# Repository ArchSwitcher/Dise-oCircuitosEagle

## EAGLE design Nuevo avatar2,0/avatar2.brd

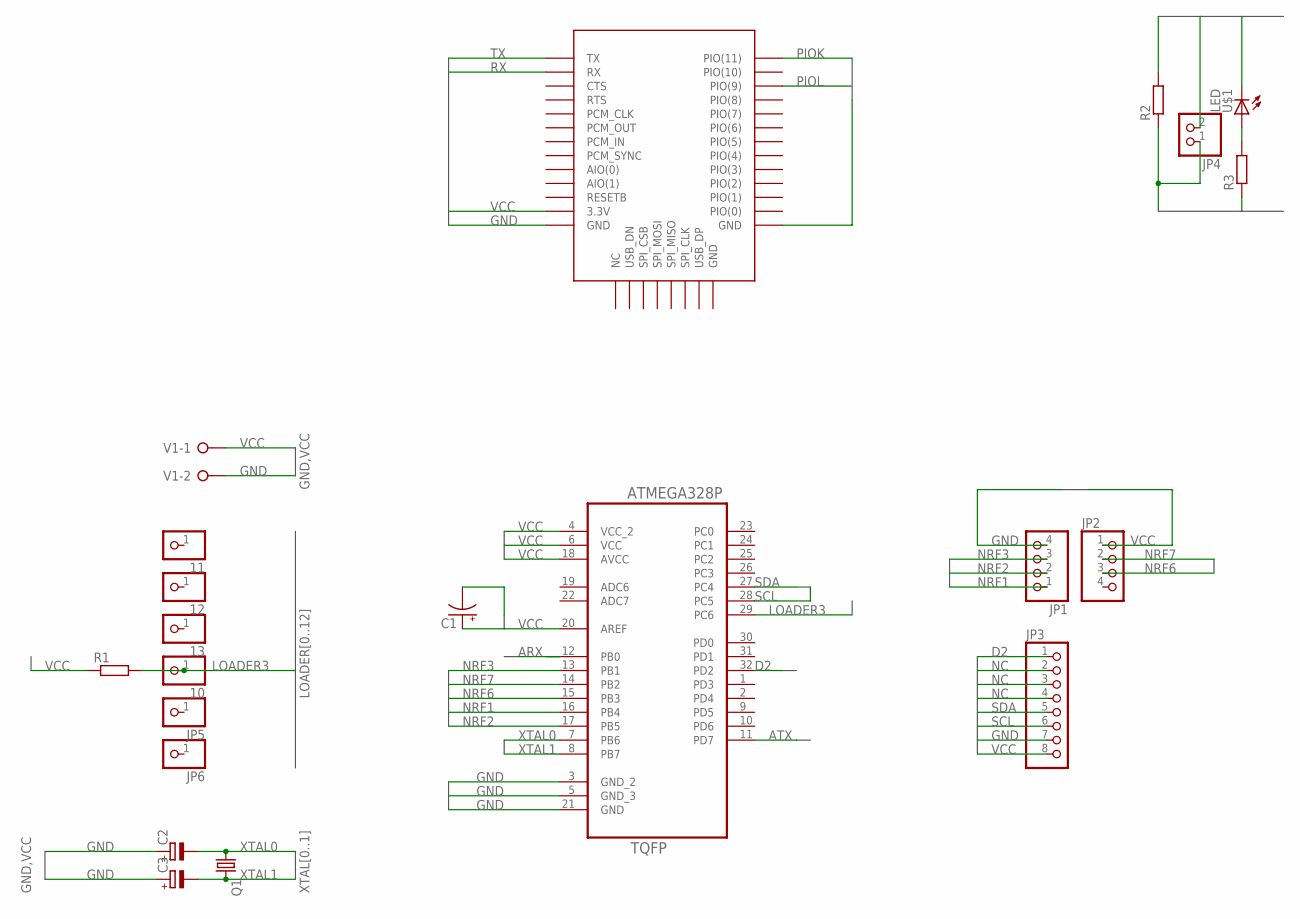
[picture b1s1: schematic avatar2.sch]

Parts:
10, 11, 12, 13: PINHD-1X1; 1X01
C1: CPOL-USTT5D7; TT5D7
C2, C3: CPOL-EUE1.8-4; E1,8-4
IC1: BC04_BLUETOOTH; BC04
JP1, JP2: PINHD-1X4; 1X04
JP3: PINHD-1X8; 1X08
JP4: PINHD-1X2; 1X02
JP5, JP6: PINHD-1X1; 1X01
Q1: CRYSTALHC49U-V; HC49U-V
R1, R2, R3: R0207/10; 0207/10
U1: ATMEGA328P-AU; QFP80P900X900X120-32N
U$1: LED; HLMP-1790
V1: W237-02P; W237-132

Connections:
ARX: U1.12 (PB0)
ATX: U1.11 (PD7)
D2: JP3.1, U1.32 (PD2)
GND: C1.-, C2.+, C3.+, IC1.P$13 (GND), IC1.P$22 (GND), JP1.4, JP3.7, R2.2, U1.3 (GND_2), U1.5 (GND_3), U1.21 (GND), U$1.C, V1.2
LOADER3: 10.1, R1.2, U1.29 (PC6)
unnamed: R3.2, U$1.A
NC: JP3.2, JP3.3, JP3.4
NRF1: JP1.1, U1.16 (PB4)
NRF2: JP1.2, U1.17 (PB5)
NRF3: JP1.3, U1.13 (PB1)
NRF6: JP2.3, U1.15 (PB3)
NRF7: JP2.2, U1.14 (PB2)
PIOK: IC1.P$34 (PIO(11)), JP4.1, R2.1
PIOL: IC1.P$32 (PIO(9)), R3.1
RX: IC1.P$2 (RX)
SCL: JP3.6, U1.28 (PC5)
SDA: JP3.5, U1.27 (PC4)
TX: IC1.P$1 (TX)
VCC: C1.+, IC1.P$12 (3.3V), JP2.1, JP3.8, JP4.2, R1.1, U1.4 (VCC_2), U1.6 (VCC), U1.18 (AVCC), U1.20 (AREF), V1.1
XTAL0: C2.-, Q1.1, U1.7 (PB6)
XTAL1: C3.-, Q1.2, U1.8 (PB7)

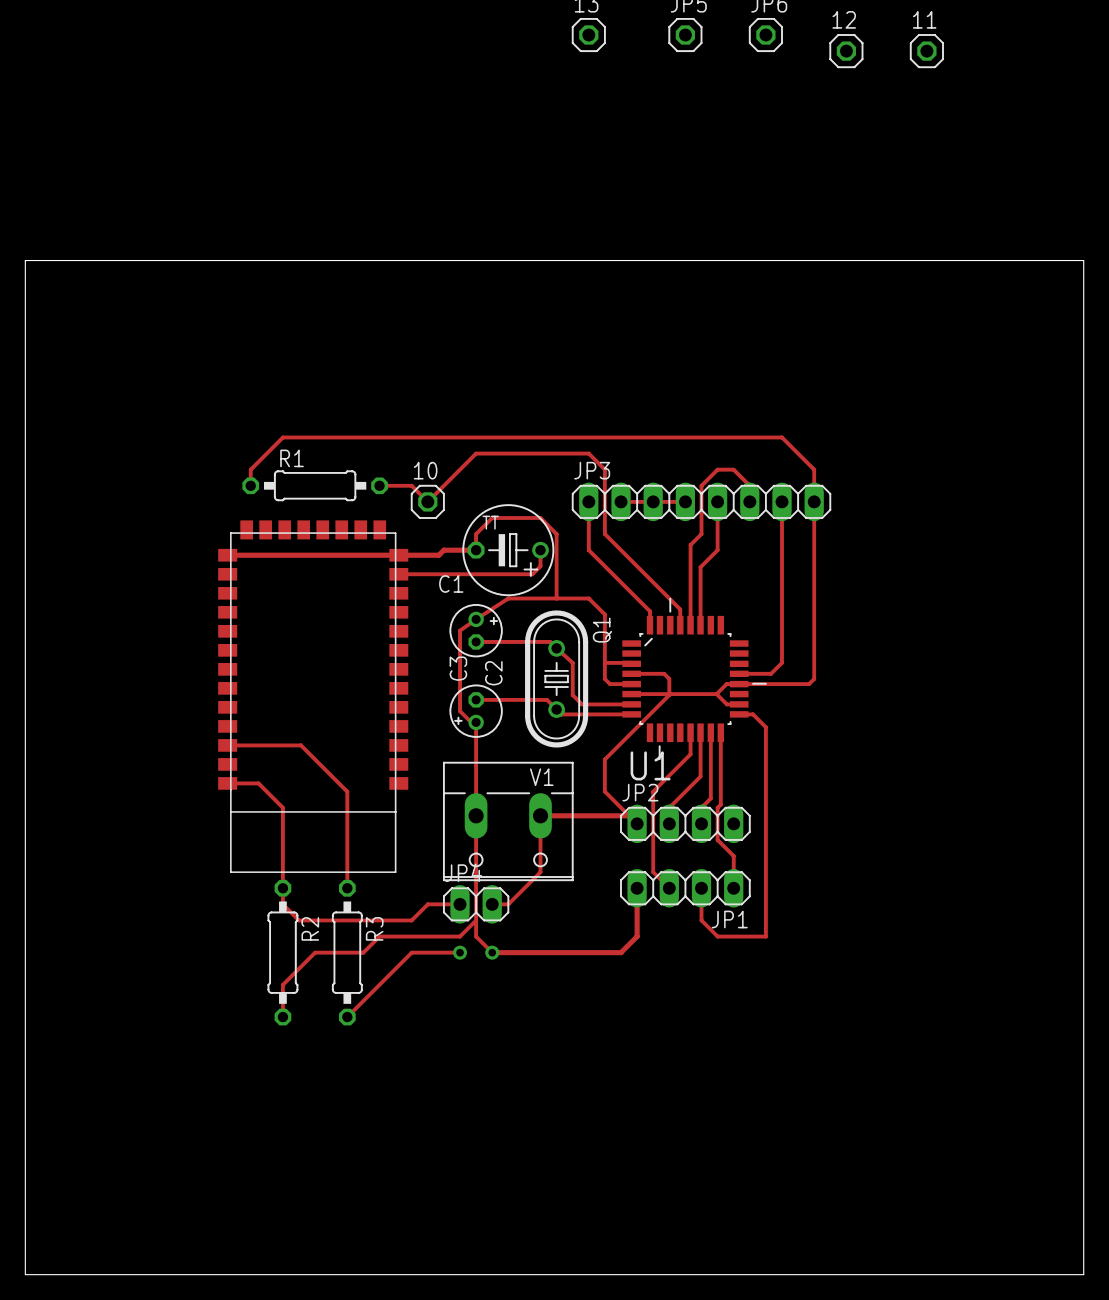
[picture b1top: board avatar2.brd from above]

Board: 2 copper layers, 83.5 x 80.0 mm, 21 parts (0 on the bottom side), 17 nets.

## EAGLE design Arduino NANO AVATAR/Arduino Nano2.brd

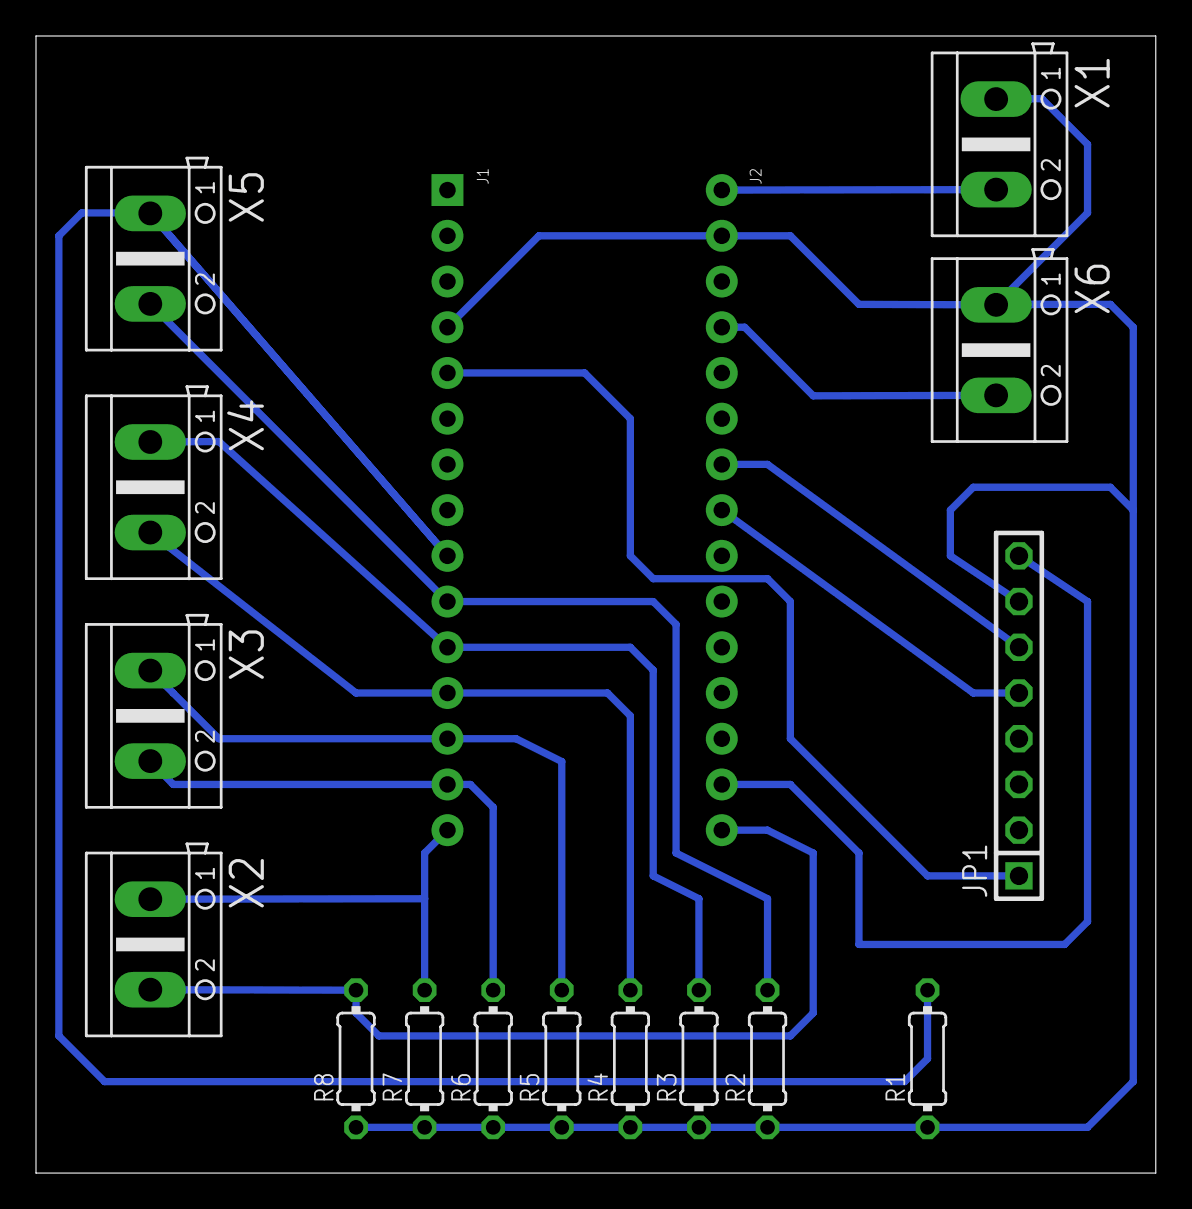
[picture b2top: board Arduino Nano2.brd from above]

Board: 2 copper layers, 62.2 x 63.2 mm, 17 parts (0 on the bottom side), 15 nets.

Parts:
J1: HEAD15-NOSS
J2: HEAD15-NOSS-1
JP1: 1X08
R1, R2, R3, R4, R5, R6, R7, R8: 0204/7
X1, X2, X3, X4, X5, X6: AK500/2

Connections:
unnamed: J2.1, X1.2
unnamed: J1.14, R6.2, X3.2
unnamed: J2.15, R8.2, X2.2
unnamed: J1.5, JP1.1
unnamed: J1.15, R7.2, X2.1
unnamed: J1.13, R5.2, X3.1
unnamed: J1.12, R4.2, X4.2
unnamed: J1.11, R3.2, X4.1
unnamed: J1.10, R2.2, X5.2
unnamed: J1.9, R1.2, X5.1
unnamed: J1.4, J2.2, JP1.7, R1.1, R2.1, R3.1, R4.1, R5.1, R6.1, R7.1, R8.1, X1.1, X6.1
unnamed: J2.14, JP1.8
unnamed: J2.4, X6.2
unnamed: J2.7, JP1.6
unnamed: J2.8, JP1.5

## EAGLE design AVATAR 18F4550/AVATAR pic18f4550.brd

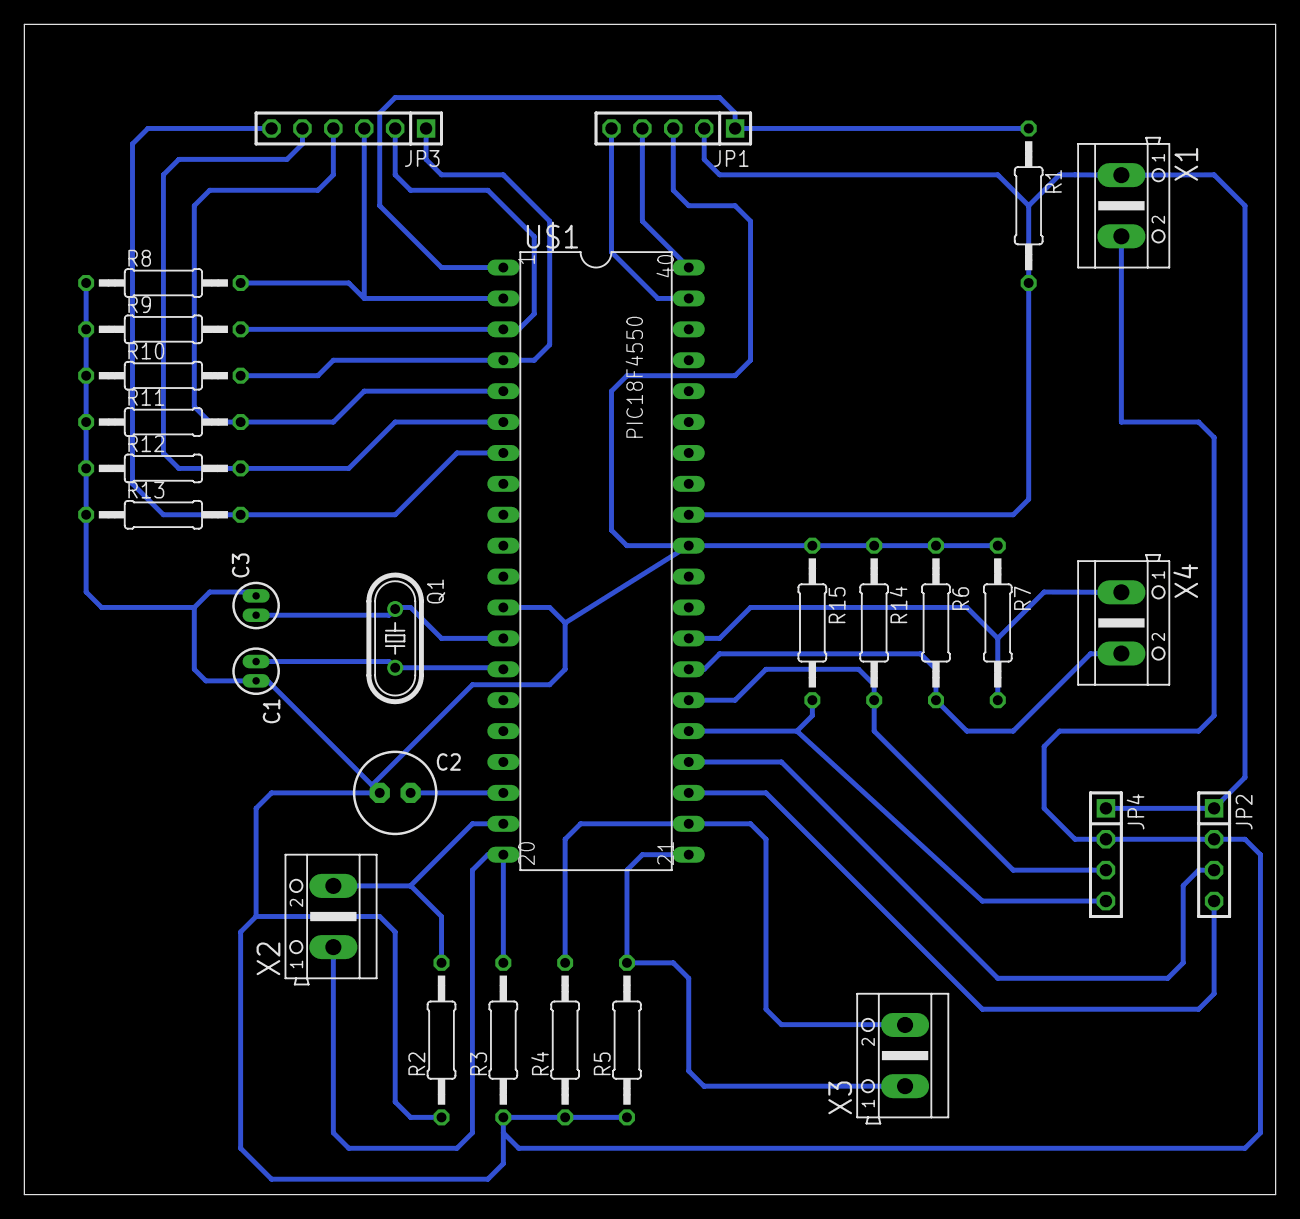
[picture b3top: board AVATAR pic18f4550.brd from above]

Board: 2 copper layers, 102.8 x 96.2 mm, 28 parts (0 on the bottom side), 24 nets.

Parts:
C1, C3: ENP-015-040
C2: ENP-025-060
JP1: 1X05
JP2, JP4: 1X04
JP3: 1X06
Q1: HC49/S
R1, R2, R3, R4, R5, R6, R7, R8, R9, R10, R11, R12, R13, R14, R15: 0207/12
U$1: PIC18F4550; PDIP-40
X1, X2, X3, X4: AK500/2

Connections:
D+: JP2.3, U$1.24
D-: JP2.4, U$1.23
GND: C1.2, C2.1, C3.2, JP1.3, JP2.2, JP4.2, R2.1, R3.1, R4.1, R5.1, R6.1, R7.1, R8.1, R9.1, R10.1, R11.1, R12.1, R13.1, R14.1, R15.1, U$1.12, U$1.31, X1.2
MCR: JP1.1, R1.1, U$1.1
unnamed: C3.1, Q1.1, U$1.13
unnamed: C1.1, Q1.2, U$1.14
unnamed: C2.2, U$1.18
PGC: JP1.5, U$1.39
PGD: JP1.4, U$1.40
RD0: R2.2, U$1.19, X2.2
RD1: R3.2, U$1.20, X2.1
RD2: R5.2, U$1.21, X3.1
RD3: R4.2, U$1.22, X3.2
RD4: R6.2, U$1.27, X4.2
RD5: R7.2, U$1.28, X4.1
RESIS0: JP3.3, R8.2, U$1.2
RESIS1: JP3.2, R9.2, U$1.3
RESIS2: JP3.1, R10.2, U$1.4
RESIS3: JP3.4, R11.2, U$1.5
RESIS4: JP3.5, R12.2, U$1.6
RESIS6: JP3.6, R13.2, U$1.7
RX: JP4.3, R14.2, U$1.26
TX: JP4.4, R15.2, U$1.25
VCC: JP1.2, JP2.1, JP4.1, R1.2, U$1.11, U$1.32, X1.1

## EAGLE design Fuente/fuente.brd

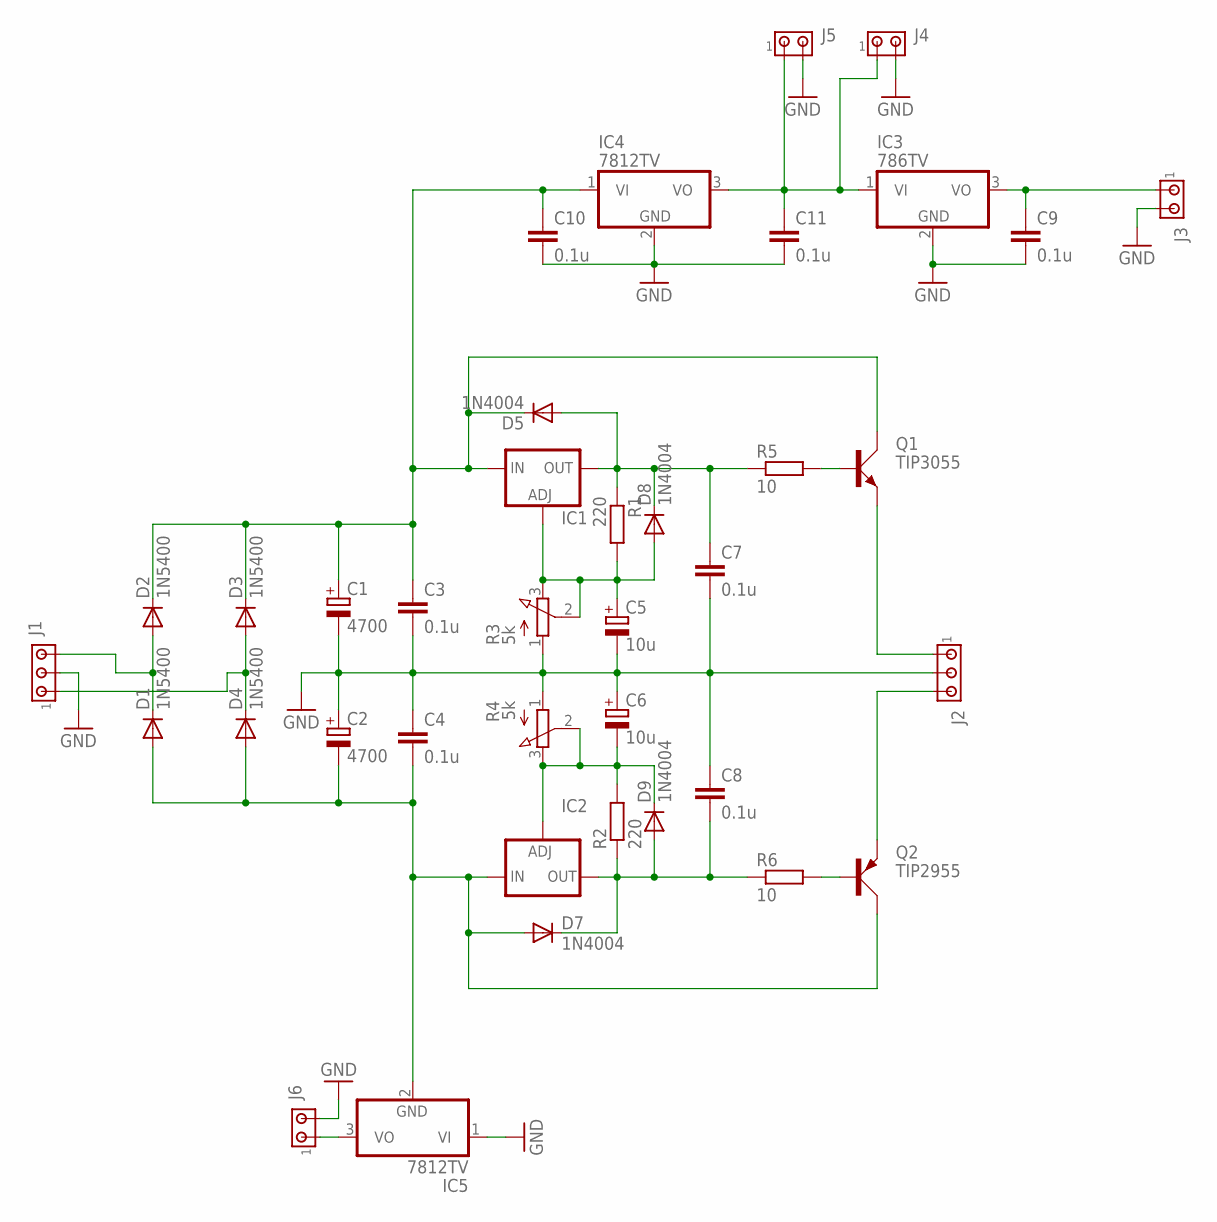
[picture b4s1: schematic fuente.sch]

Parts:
C1, C2: 4700; EB22,5D
C3, C4, C7, C8, C9, C10, C11: 0.1u; C025-024X044
C5, C6: 10u; E2,5-5
D1, D2, D3, D4: 1N5400; DO201-15
D5, D7, D8, D9: 1N4004; DO41-10
IC1: LM317TS; 317TS
IC2: LM337TS; 337TS
IC3: 786TV; TO220V
IC4, IC5: 7812TV; TO220V
J1, J2: MTA03-156; 1X3MTA
J3, J4, J5, J6: MTA02-100; 10X02MTA
Q1: TIP3055; TOP3AV
Q2: TIP2955; TOP3AV
R1, R2: 220; 0204/7
R3, R4: 5k; 3RP/1610N
R5, R6: 10; 0204/7

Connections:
GND: C1.-, C2.+, C3.2, C4.1, C5.-, C6.+, C7.2, C8.1, C9.2, C10.2, C11.2, IC3.2 (GND), IC4.2 (GND), IC5.1 (VI), J1.2, J2.2, J3.2, J4.2, J5.2, J6.2, R3.1 (A), R4.1 (A)
unnamed: C11.1, IC3.1 (VI), IC4.3 (VO), J4.1, J5.1
unnamed: D1.C, D2.A, J1.3
unnamed: D3.A, D4.C, J1.1
unnamed: C2.-, C4.2, D1.A, D4.A, D7.A, IC2.2 (IN), IC5.2 (GND), Q2.C
unnamed: C7.1, D5.A, D8.C, IC1.2 (OUT), R1.1, R5.1
unnamed: C5.+, D8.A, IC1.1 (ADJ), R1.2, R3.2 (S), R3.3 (E)
unnamed: J2.3, Q2.E
unnamed: IC5.3 (VO), J6.1
unnamed: Q2.B, R6.2
unnamed: C8.2, D7.C, D9.A, IC2.3 (OUT), R2.1, R6.1
unnamed: C6.-, D9.C, IC2.1 (ADJ), R2.2, R4.2 (S), R4.3 (E)
unnamed: C1.+, C3.1, C10.1, D2.C, D3.C, D5.C, IC1.3 (IN), IC4.1 (VI), Q1.C
unnamed: Q1.B, R5.2
unnamed: J2.1, Q1.E
unnamed: C9.1, IC3.3 (VO), J3.1

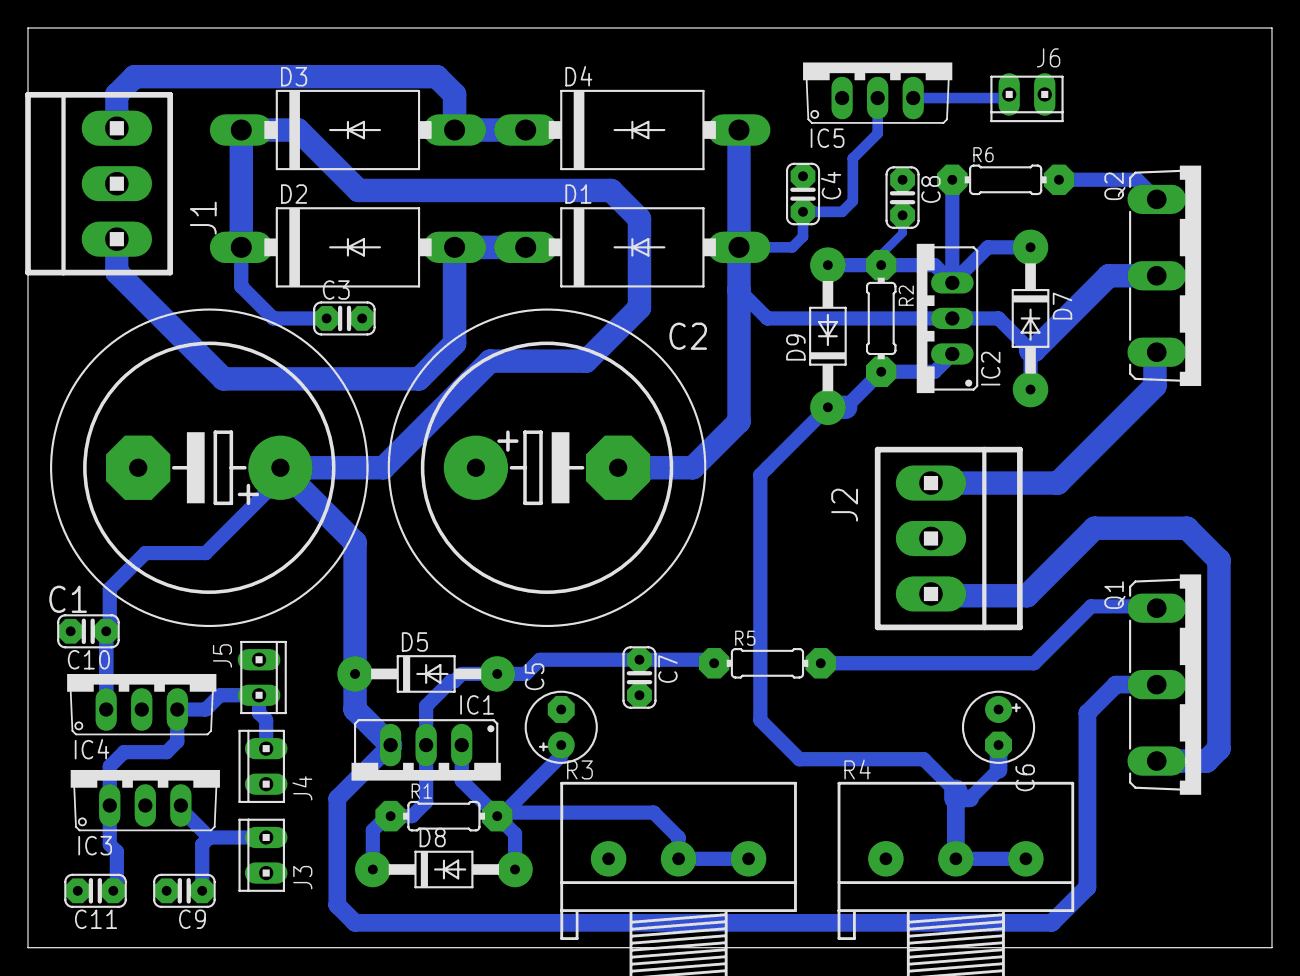
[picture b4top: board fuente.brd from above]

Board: 2 copper layers, 88.9 x 65.7 mm, 38 parts (0 on the bottom side), 16 nets.

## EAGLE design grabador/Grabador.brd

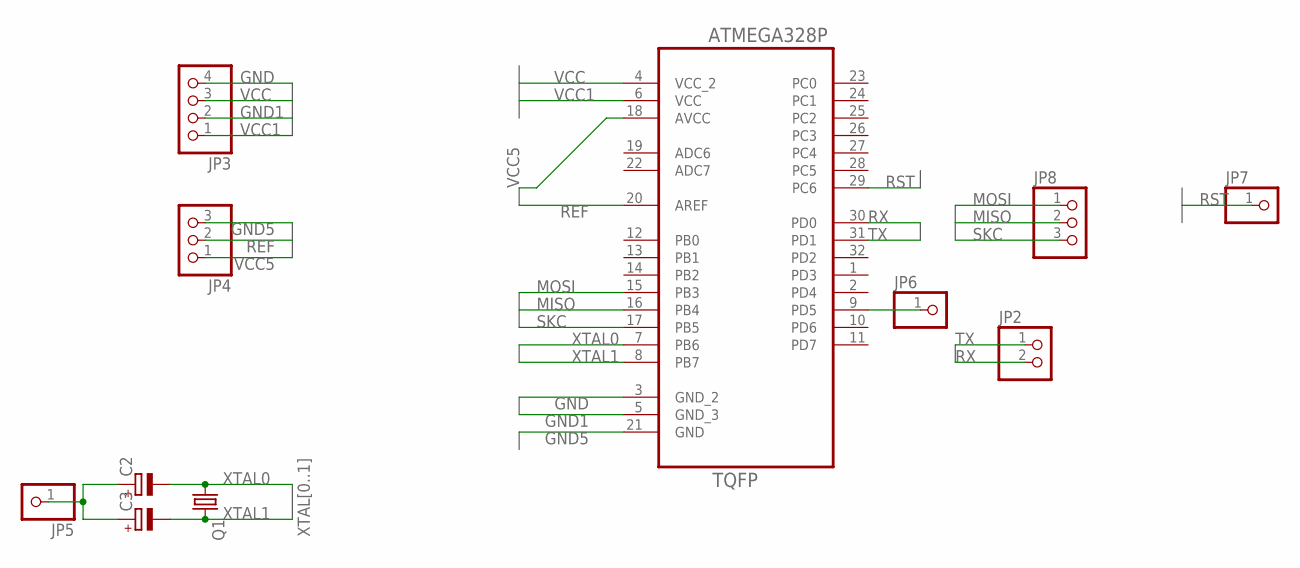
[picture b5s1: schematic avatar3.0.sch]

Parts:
C2, C3: CPOL-EUE1.8-4; E1,8-4
JP2: PINHD-1X2; 1X02
JP3: PINHD-1X4; 1X04
JP4, JP8: PINHD-1X3; 1X03
JP5, JP6, JP7: PINHD-1X1; 1X01
Q1: CRYSTALHC49U-V; HC49U-V
U1: ATMEGA328P-AU; QFP80P900X900X120-32N

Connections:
GND: JP3.4, U1.3 (GND_2)
GND1: JP3.2, U1.5 (GND_3)
GND5: JP4.3, U1.21 (GND)
MISO: JP8.2, U1.16 (PB4)
MOSI: JP8.1, U1.15 (PB3)
unnamed: C2.+, C3.+, JP5.1
unnamed: JP6.1, U1.9 (PD5)
REF: JP4.2, U1.20 (AREF)
RST: JP7.1, U1.29 (PC6)
RX: JP2.2, U1.30 (PD0)
SKC: JP8.3, U1.17 (PB5)
TX: JP2.1, U1.31 (PD1)
VCC: JP3.3, U1.4 (VCC_2)
VCC1: JP3.1, U1.6 (VCC)
VCC5: JP4.1, U1.18 (AVCC)
XTAL0: C2.-, Q1.1, U1.7 (PB6)
XTAL1: C3.-, Q1.2, U1.8 (PB7)

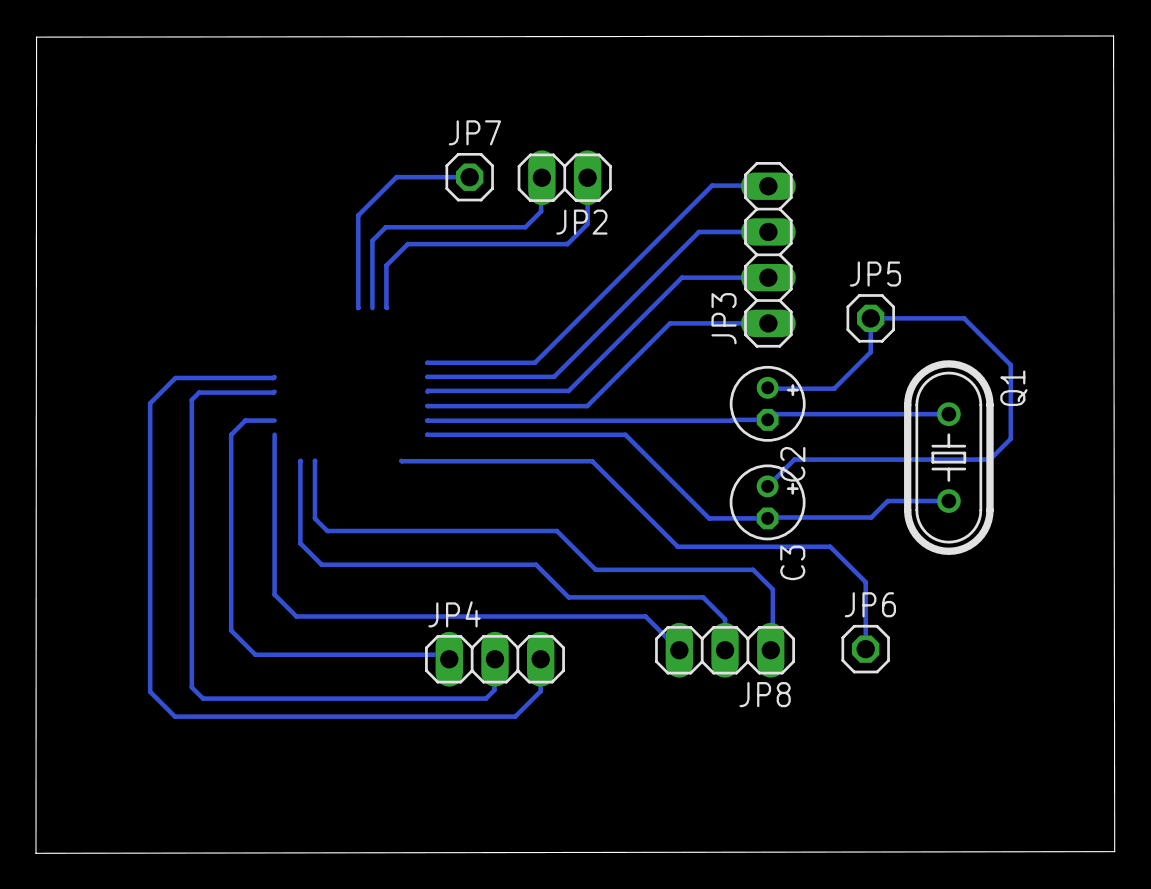
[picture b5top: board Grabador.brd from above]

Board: 2 copper layers, 59.9 x 45.4 mm, 11 parts (1 on the bottom side), 17 nets.

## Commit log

2020-07-03 First Upload
